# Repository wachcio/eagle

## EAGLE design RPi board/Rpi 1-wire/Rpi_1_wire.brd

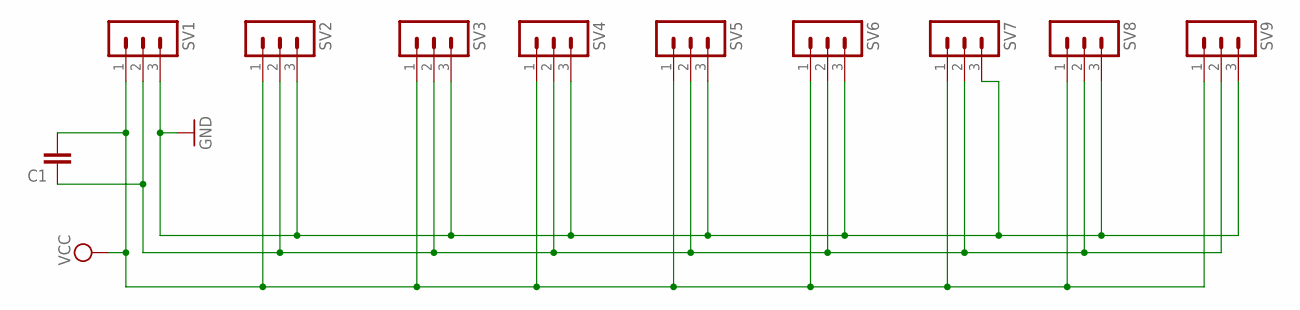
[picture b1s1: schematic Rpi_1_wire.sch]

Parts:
C1: C-EUC0805; C0805
SV1, SV2, SV3, SV4, SV5, SV6, SV7, SV8, SV9: MA03-1

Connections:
GND: SV1.3, SV2.3, SV3.3, SV4.3, SV5.3, SV6.3, SV7.3, SV8.3, SV9.3
unnamed: C1.1, SV1.2, SV2.2, SV3.2, SV4.2, SV5.2, SV6.2, SV7.2, SV8.2, SV9.2
VCC: C1.2, SV1.1, SV2.1, SV3.1, SV4.1, SV5.1, SV6.1, SV7.1, SV8.1, SV9.1

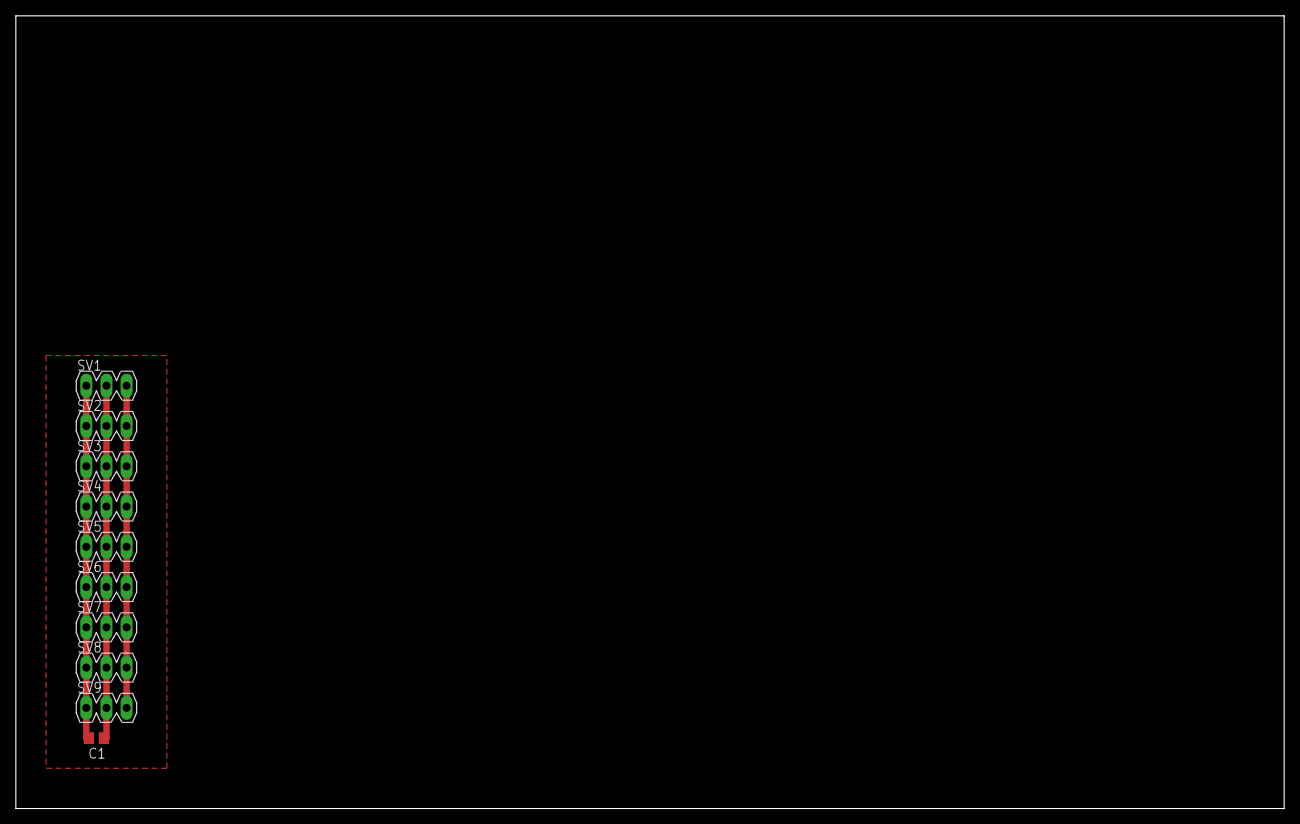
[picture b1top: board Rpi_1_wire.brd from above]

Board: 2 copper layers, 160.0 x 100.0 mm, 10 parts (0 on the bottom side), 3 nets.

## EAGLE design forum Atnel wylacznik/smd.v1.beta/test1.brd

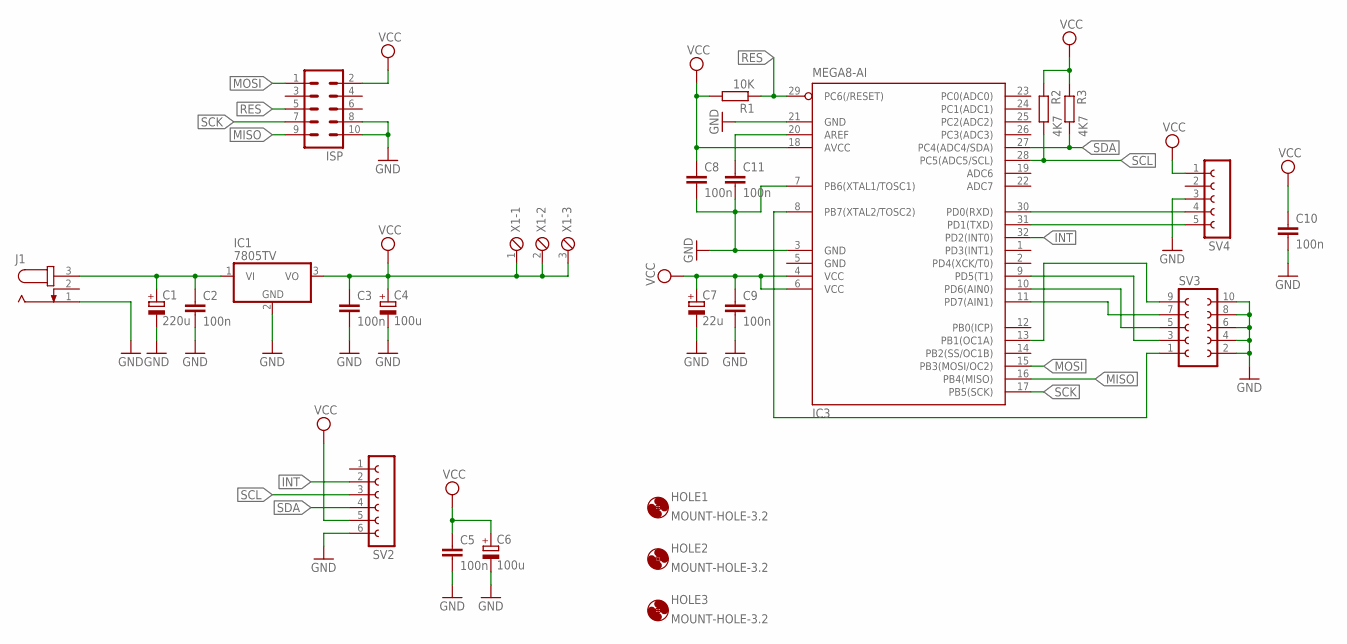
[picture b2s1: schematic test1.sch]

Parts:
C1: 220u; E3,5-8
C2, C3, C5, C8, C9, C10, C11: 100n; C0805
C4, C6: 100u; E2,5-5
C7: 22u; E2,5-5
HOLE1, HOLE2, HOLE3: MOUNT-HOLE-3.2; 3,2
IC1: 7805TV; TO220V
IC3: MEGA8-AI; TQFP32-08
ISP: ML10
J1: JACK-PLUG1; SPC4078
R1: 10K; R0805
R2, R3: 4K7; R0805
SV2: FE06-1; FE06
SV3: FE05-2
SV4: FE05-1
X1: MPT3; 3POL254

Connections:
GND: C1.-, C2.2, C3.2, C4.-, C5.2, C6.-, C7.-, C8.2, C9.2, C10.2, C11.2, IC1.2 (GND), IC3.3 (GND), IC3.5 (GND), IC3.7 (PB6(XTAL1/TOSC1)), IC3.21 (GND), ISP.8, ISP.10, J1.1, SV2.6, SV3.2, SV3.4, SV3.6, SV3.8, SV3.10, SV4.3
INT: IC3.32 (PD2(INT0)), SV2.2
MISO: IC3.16 (PB4(MISO)), ISP.9
MOSI: IC3.15 (PB3(MOSI/OC2)), ISP.1
unnamed: C1.+, C2.1, IC1.1 (VI), J1.3
unnamed: C11.1, IC3.20 (AREF)
unnamed: IC3.30 (PD0(RXD)), SV4.4
unnamed: IC3.31 (PD1(TXD)), SV4.5
unnamed: IC3.8 (PB7(XTAL2/TOSC2)), SV3.1
unnamed: IC3.13 (PB1(OC1A)), SV3.9
unnamed: IC3.11 (PD7(AIN1)), SV3.7
unnamed: IC3.10 (PD6(AIN0)), SV3.5
unnamed: IC3.9 (PD5(T1)), SV3.3
RES: IC3.29 (PC6(/RESET)), ISP.5, R1.1
SCK: IC3.17 (PB5(SCK)), ISP.7
SCL: IC3.28 (PC5(ADC5/SCL)), R2.2, SV2.3
SDA: IC3.27 (PC4(ADC4/SDA)), R3.2, SV2.4
VCC: C3.1, C4.+, C5.1, C6.+, C7.+, C8.1, C9.1, C10.1, IC1.3 (VO), IC3.4 (VCC), IC3.6 (VCC), IC3.18 (AVCC), ISP.2, R1.2, R2.1, R3.1, SV2.5, SV4.1, X1.1, X1.2, X1.3

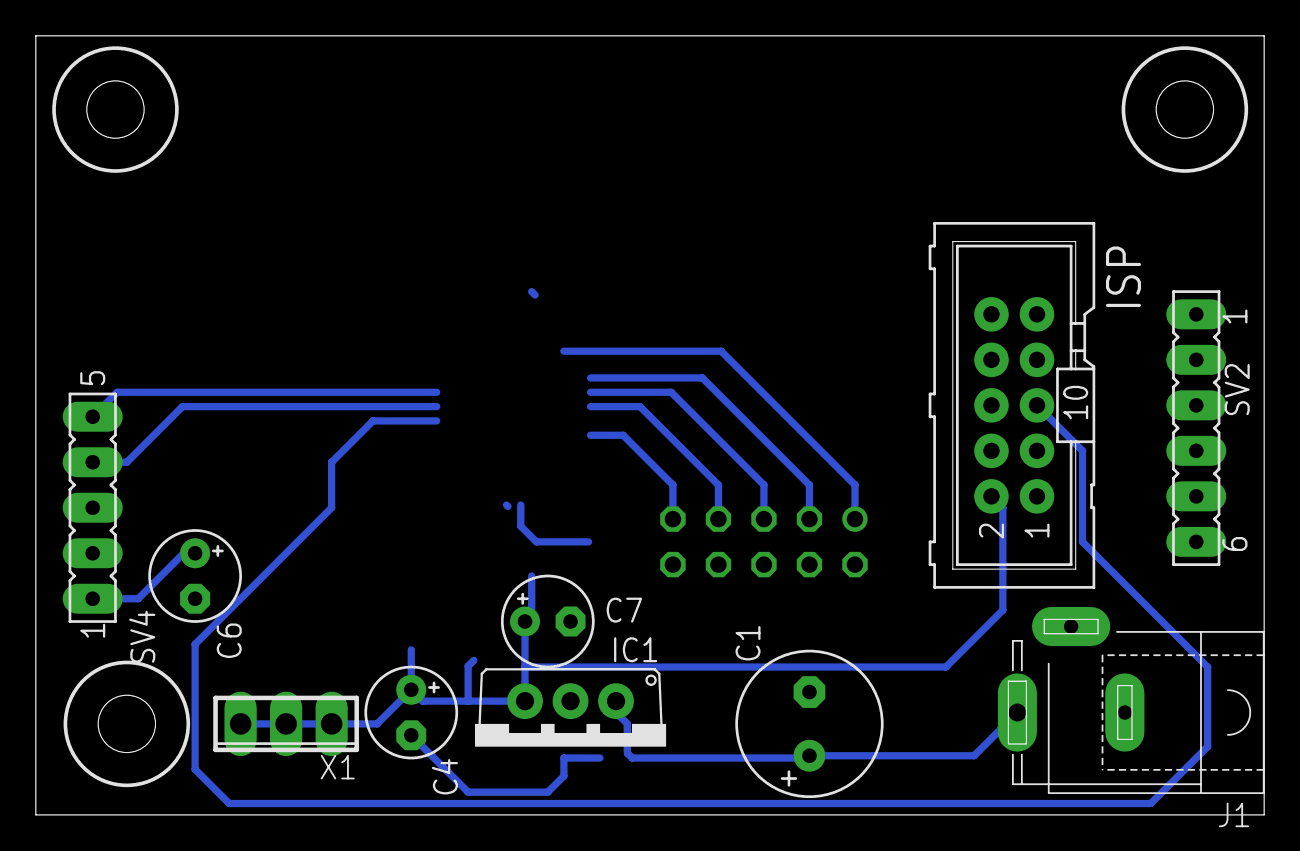
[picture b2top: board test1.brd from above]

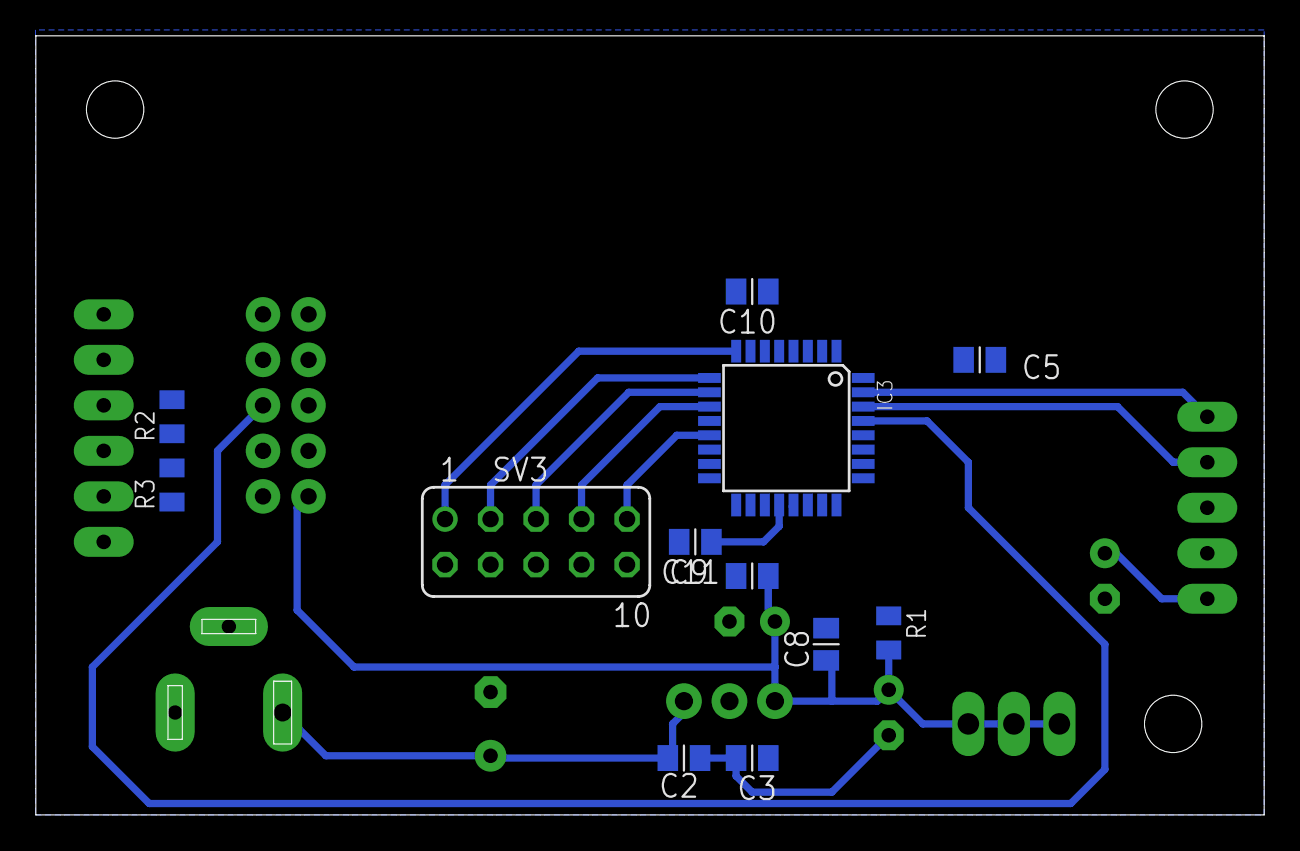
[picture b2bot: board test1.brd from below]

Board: 2 copper layers, 68.6 x 43.5 mm, 25 parts (12 on the bottom side), 18 nets.

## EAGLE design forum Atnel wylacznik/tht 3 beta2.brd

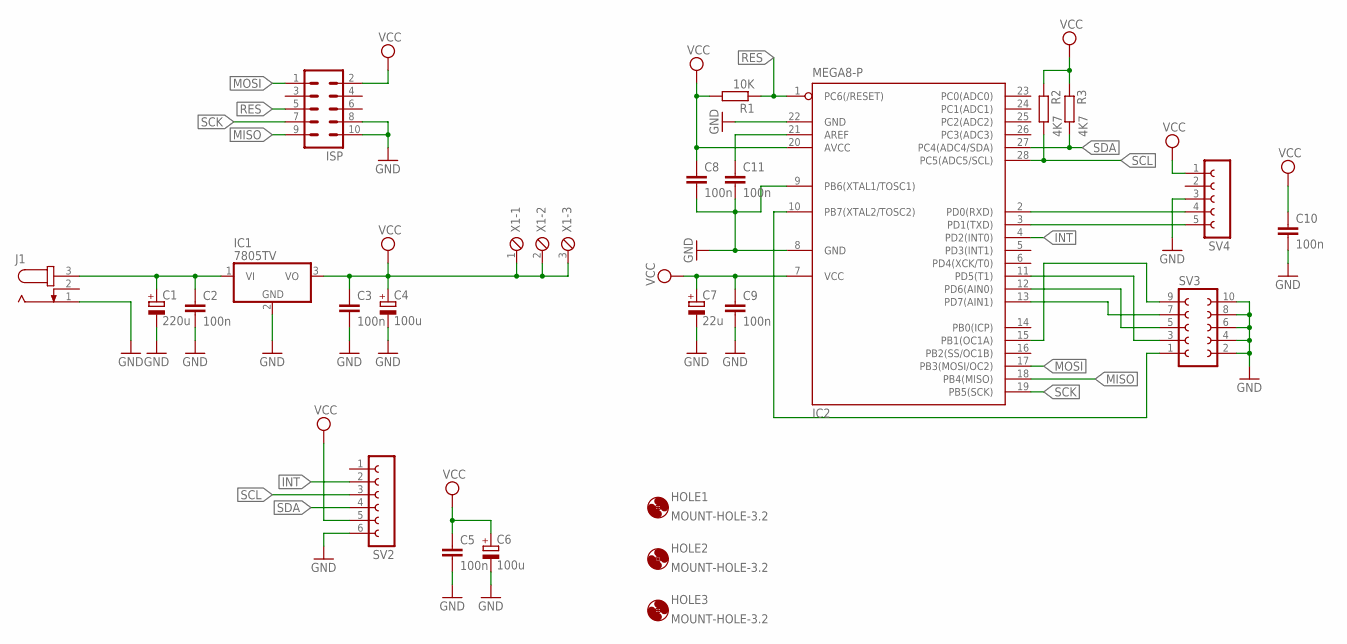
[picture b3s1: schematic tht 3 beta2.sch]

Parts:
C1: 220u; E3,5-8
C2, C3, C5, C8, C10, C11: 100n; C025-025X050
C4, C6: 100u; E2,5-5
C7: 22u; E2,5-5
C9: 100n; C025-030X050
HOLE1, HOLE2, HOLE3: MOUNT-HOLE-3.2; 3,2
IC1: 7805TV; TO220V
IC2: MEGA8-P; DIL28-3
ISP: ML10
J1: JACK-PLUG1; SPC4078
R1: 10K; 0204/7
R2, R3: 4K7; 0204/7
SV2: FE06-1; FE06
SV3: FE05-2
SV4: FE05-1
X1: MPT3; 3POL254

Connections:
GND: C1.-, C2.2, C3.2, C4.-, C5.2, C6.-, C7.-, C8.2, C9.2, C10.2, C11.2, IC1.2 (GND), IC2.8 (GND), IC2.9 (PB6(XTAL1/TOSC1)), IC2.22 (GND), ISP.8, ISP.10, J1.1, SV2.6, SV3.2, SV3.4, SV3.6, SV3.8, SV3.10, SV4.3
INT: IC2.4 (PD2(INT0)), SV2.2
MISO: IC2.18 (PB4(MISO)), ISP.9
MOSI: IC2.17 (PB3(MOSI/OC2)), ISP.1
unnamed: C1.+, C2.1, IC1.1 (VI), J1.3
unnamed: C11.1, IC2.21 (AREF)
unnamed: IC2.2 (PD0(RXD)), SV4.4
unnamed: IC2.3 (PD1(TXD)), SV4.5
unnamed: IC2.10 (PB7(XTAL2/TOSC2)), SV3.1
unnamed: IC2.15 (PB1(OC1A)), SV3.9
unnamed: IC2.13 (PD7(AIN1)), SV3.7
unnamed: IC2.12 (PD6(AIN0)), SV3.5
unnamed: IC2.11 (PD5(T1)), SV3.3
RES: IC2.1 (PC6(/RESET)), ISP.5, R1.1
SCK: IC2.19 (PB5(SCK)), ISP.7
SCL: IC2.28 (PC5(ADC5/SCL)), R2.2, SV2.3
SDA: IC2.27 (PC4(ADC4/SDA)), R3.2, SV2.4
VCC: C3.1, C4.+, C5.1, C6.+, C7.+, C8.1, C9.1, C10.1, IC1.3 (VO), IC2.7 (VCC), IC2.20 (AVCC), ISP.2, R1.2, R2.1, R3.1, SV2.5, SV4.1, X1.1, X1.2, X1.3

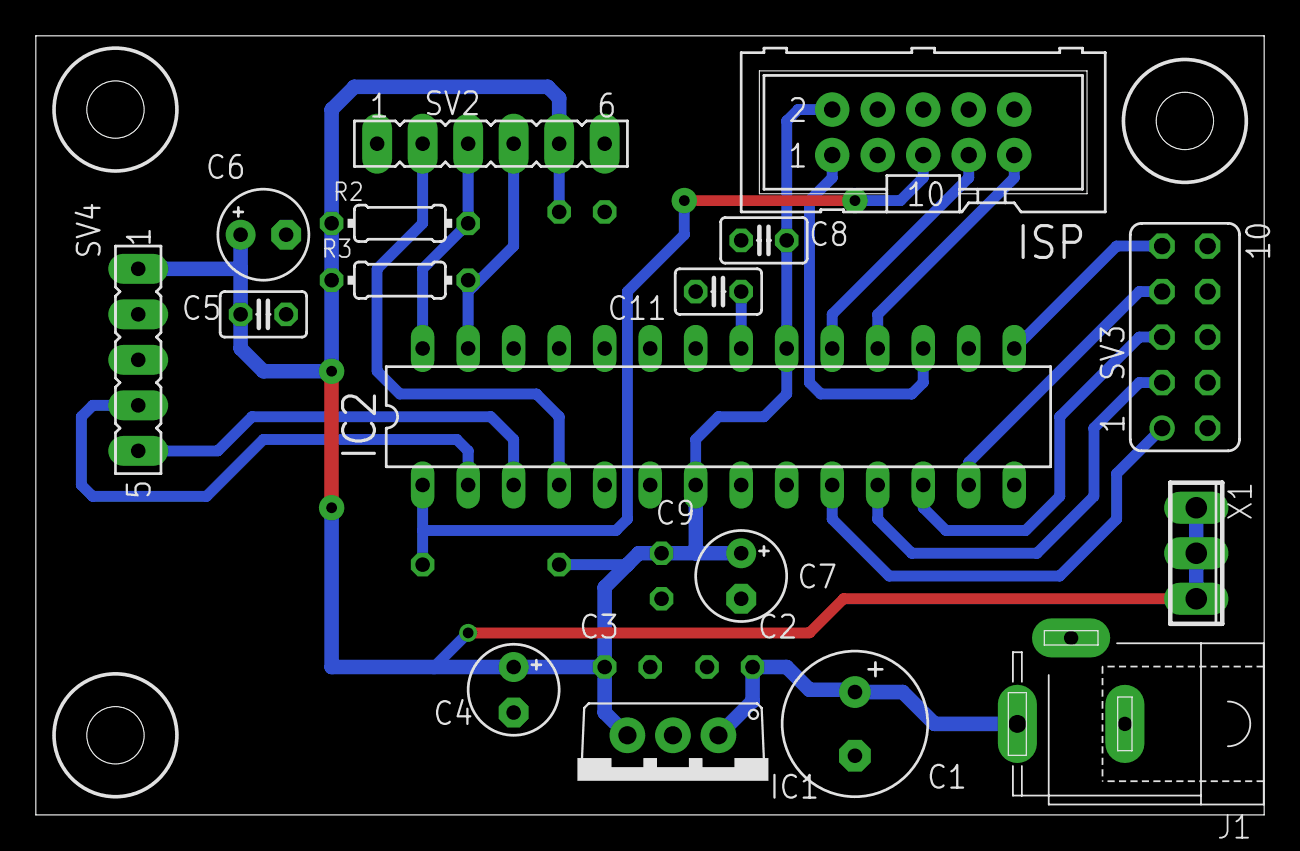
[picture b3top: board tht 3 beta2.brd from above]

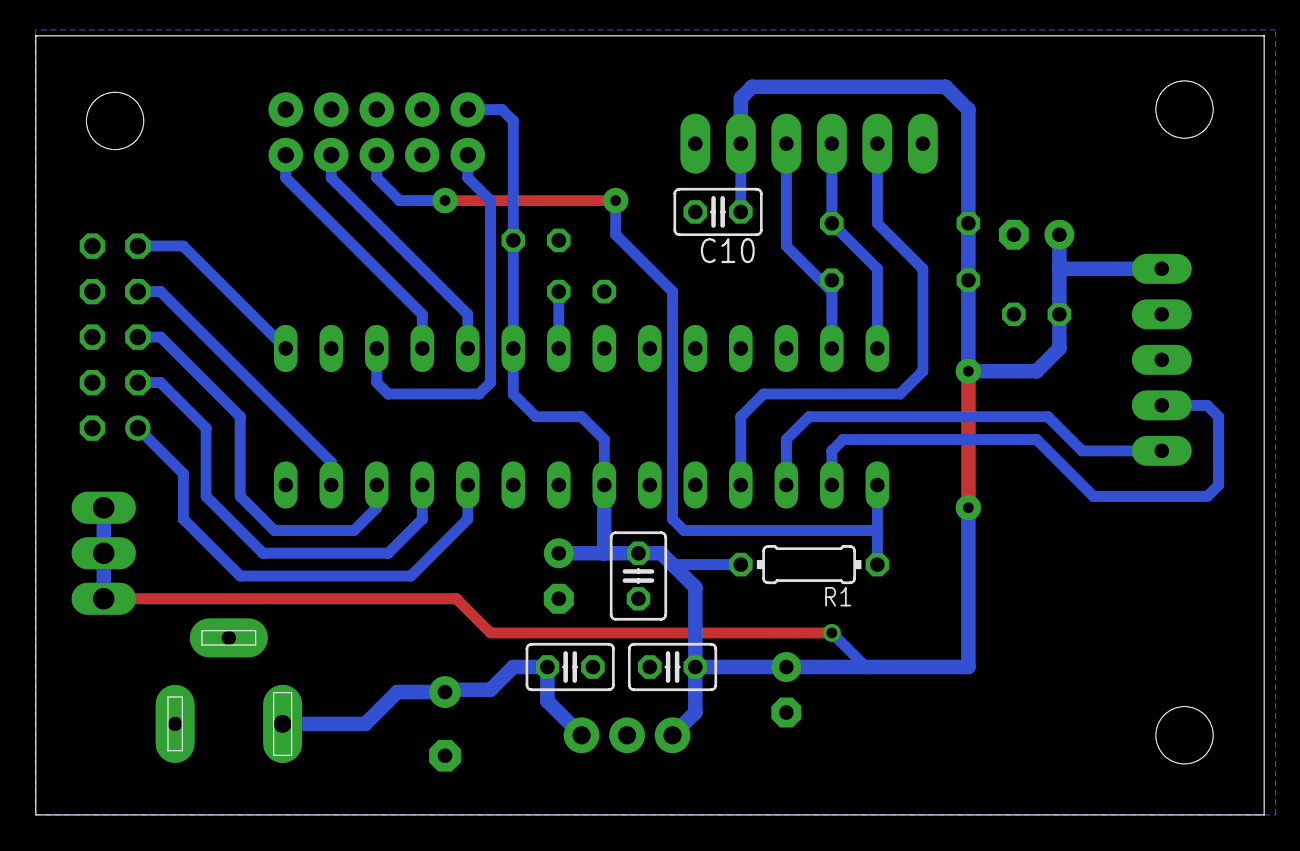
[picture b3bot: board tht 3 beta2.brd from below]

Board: 2 copper layers, 68.6 x 43.5 mm, 25 parts (5 on the bottom side), 18 nets.

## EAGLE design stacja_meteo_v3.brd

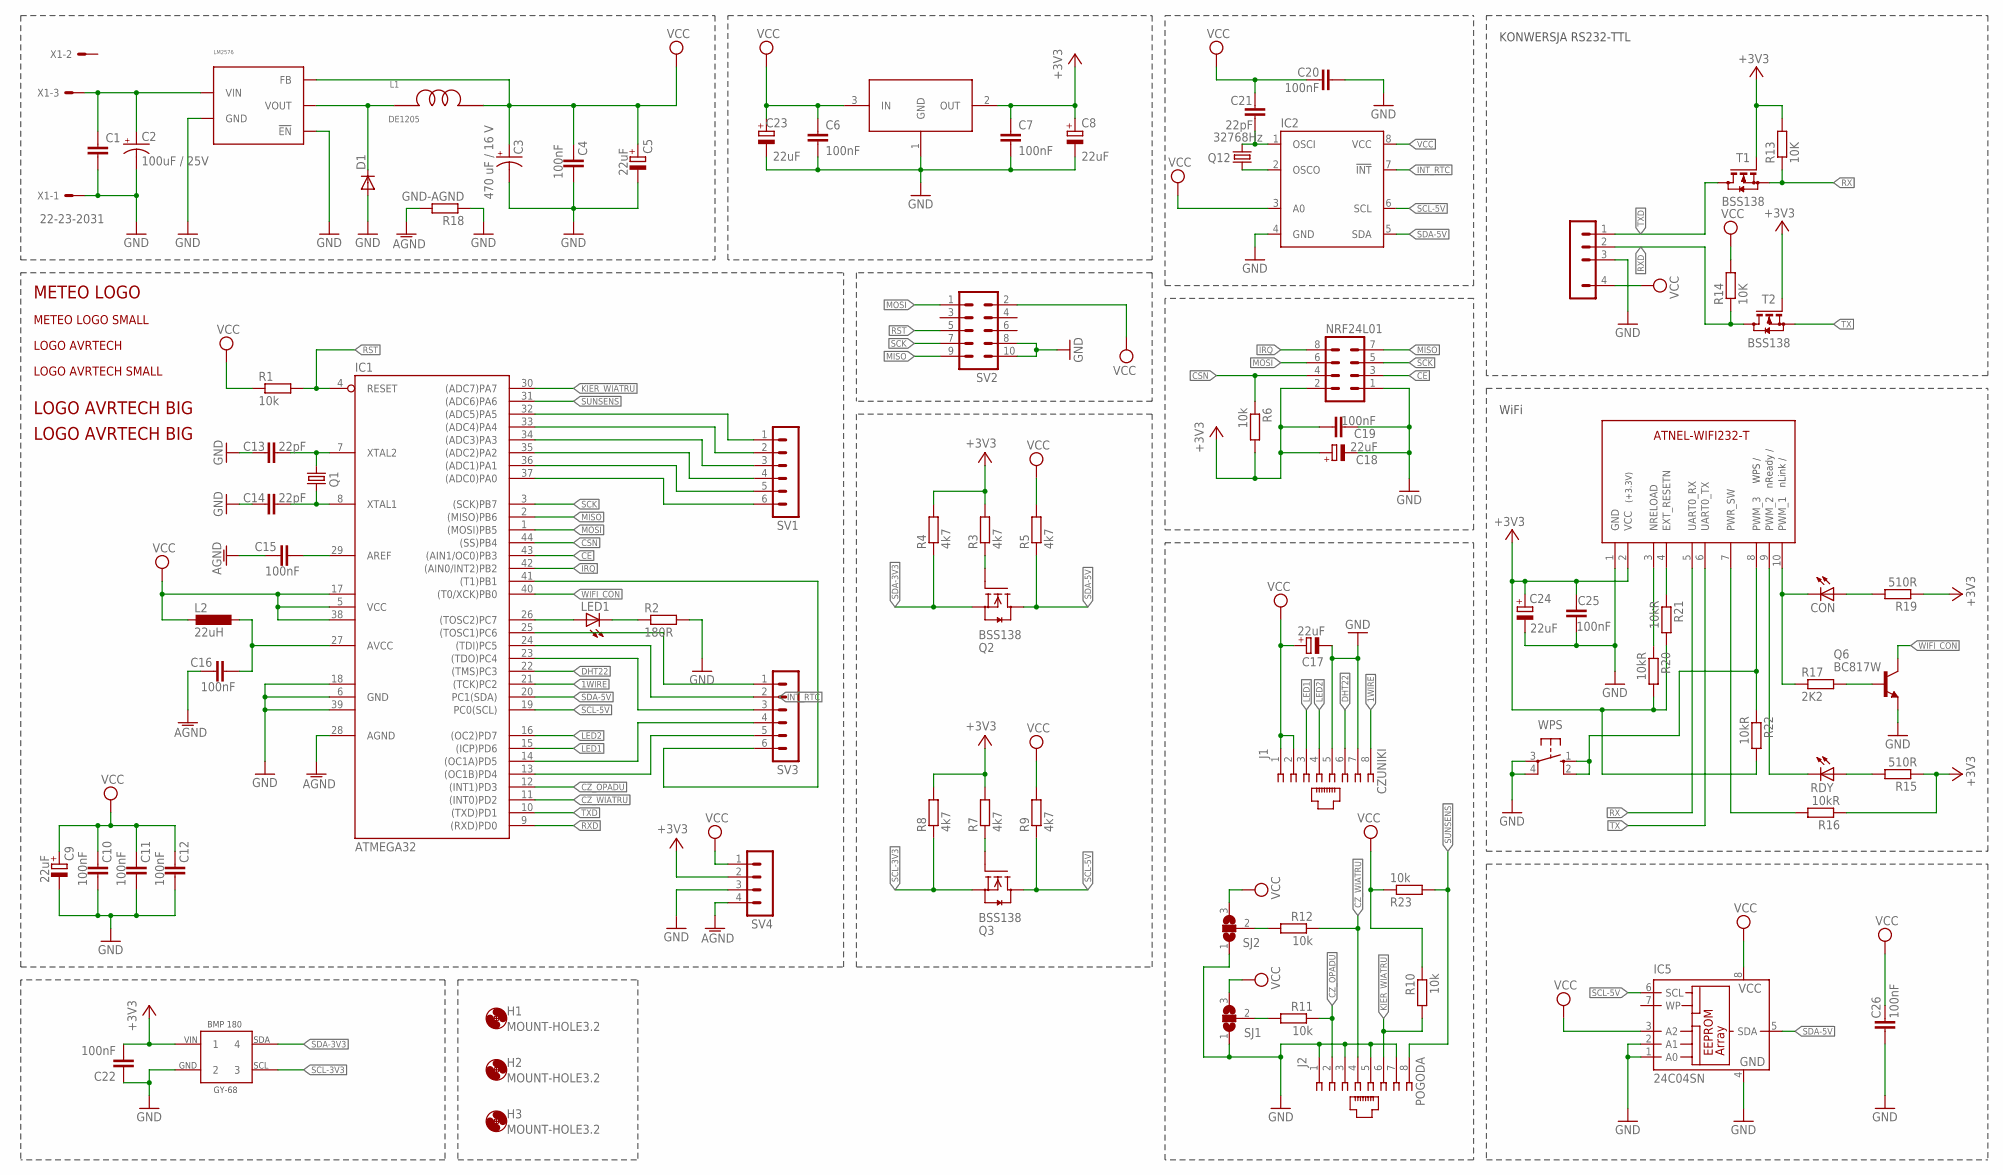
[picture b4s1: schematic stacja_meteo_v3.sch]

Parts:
BMP1: GY-68
C1: C-EUC1206; C1206
C2: 100uF / 25V; PANASONIC_D
C3: 470 uF / 16 V; PANASONIC_E
C4, C10, C11, C12, C15, C16, C22: 100nF; C1206
C5, C8, C9, C17, C18, C23, C24: 22uF; SMC_A
C6, C7, C19, C25: 100nF; C0805
C13, C14: 22pF; C0805K
C20, C26: 100nF; C1206K
C21: 22pF; C1206K
CON: LEDSML0805; SML0805
D1: DIODE-SMC; SMC
H1, H2, H3: MOUNT-HOLE3.2; 3,2
IC1: ATMEGA32; TQFP44
IC2: RTC_PCF8583T; SO08
IC5: 24C04SN; SO-08
J1: CZUNIKI; 556416-1
J2: POGODA; 556416-1
L1: DE1205
L2: 22uH; IR-2
LED1: LED5MM
LM1117/1: LM1117-3.3; SOT223
LM2576: LM2576D2PAK-5; D2PAK-5
NRF24L01: ML10
Q1: 11.059 MHz; CSM-7X-DU
Q2, Q3: BSS138; SOT23
Q6: BC817W; SOT23-BEC
Q12: 32768Hz; MC-406
R1, R10, R11, R12, R23: 10k; R0603
R2: 180R; R0805
R3, R4, R5, R7, R8, R9: 4k7; R0805
R6: 10k; R0805W
R13, R14: 10K; R0805
R15, R19: 510R; R0603
R16, R20, R21, R22: 10kR; R0603
R17: 2K2; R0603
R18: GND-AGND; R0805
RDY: LEDSML0805; SML0805
RS232-TTL: ATB-BTM-222
SJ1, SJ2: SJ2W; SJ_2
SV1, SV3: MA06-1
SV2: ML10
SV4: MA04-1
T1, T2: BSS138; SOT23
U$2: ATNEL-WIFI232-T_2
U$3: METEO_LOGO; LOGO_METEO
U$4: METEO_LOGO_SMALL; LOGO_METEO_SMALL
U$6: LOGO_AVRTECH
U$7: LOGO_AVRTECH_SMALL
U$8, U$9: LOGO_AVRTECH_BIG; LOGOAVRTECHBIG
WPS: 10-XX; B3F-10XX
X1: 22-23-2031

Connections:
1WIRE: IC1.21 ((TCK)PC2), J1.8
+3V3: BMP1.1, C7.1, C8.+, C18.+, C19.1, C22.2, C24.+, C25.1, LM1117/1.2 (OUT), NRF24L01.2, R3.2, R4.2, R6.2, R7.2, R8.2, R13.2, R15.1, R16.1, R19.1, R20.2, R21.2, R22.2, SV4.2, T1.1 (G), T2.1 (G), U$2.2 (VCC)
AGND: C15.1, C16.1, IC1.28 (AGND), R18.2, SV4.4
CE: IC1.43 ((AIN1/OC0)PB3), NRF24L01.3
CSN: IC1.44 ((SS)PB4), NRF24L01.4, R6.1
CZ_OPADU: IC1.12 ((INT1)PD3), J2.2, R11.1
CZ_WIATRU: IC1.11 ((INT0)PD2), J2.4, R12.1
DHT22: IC1.22 ((TMS)PC3), J1.6
GND: BMP1.2, C1.2, C2.-, C3.-, C4.2, C5.-, C6.2, C7.2, C8.-, C9.-, C10.2, C11.2, C12.2, C13.1, C14.1, C17.-, C18.-, C19.2, C20.2, C22.1, C23.-, C24.-, C25.2, C26.2, D1.A, IC1.6 (GND), IC1.18 (GND1), IC1.39 (GND2), IC2.4 (GND), IC5.1 (A0), IC5.2 (A1), IC5.4 (GND), J1.5, J1.7, J2.1, J2.3, J2.5, J2.7, LM1117/1.1 (GND), LM2576.P$3 (GND), LM2576.P$5 (!EN), LM2576.P$6 (GND), NRF24L01.1, Q6.E, R2.2, R18.1, RS232-TTL.3 (GND), SJ1.1, SJ2.1, SV2.8, SV2.10, SV4.3, U$2.1 (GND), WPS.3, WPS.4 (P1), X1.1
INT_RTC: IC1.24 ((TDI)PC5), IC2.7 (!INT), SV3.2
IRQ: IC1.42 ((AIN0/INT2)PB2), NRF24L01.8
KIER_WIATRU: IC1.30 ((ADC7)PA7), J2.6, R10.2
LED1: IC1.15 ((ICP)PD6), J1.3
LED2: IC1.16 ((OC2)PD7), J1.4
MISO: IC1.2 ((MISO)PB6), NRF24L01.7, SV2.9
MOSI: IC1.1 ((MOSI)PB5), NRF24L01.6, SV2.1
unnamed: C15.2, IC1.29 (AREF)
unnamed: IC1.26 ((TOSC2)PC7), LED1.A
unnamed: C16.2, IC1.27 (AVCC), L2.1
unnamed: LED1.K (C), R2.1
unnamed: Q2.1 (G), R3.1
unnamed: C13.2, IC1.7 (XTAL2), Q1.2
unnamed: C14.2, IC1.8 (XTAL1), Q1.1
unnamed: R15.2, RDY.A
unnamed: R12.2, SJ2.2
unnamed: R11.2, SJ1.2
unnamed: RDY.C, U$2.9 (PWM_2)
unnamed: Q3.1 (G), R7.1
unnamed: R16.2, U$2.7 (PWR_SW)
unnamed: R20.1, U$2.3 (NRELOAD)
unnamed: R21.1, U$2.4 (EXT_RESETN)
unnamed: IC1.32 ((ADC5)PA5), SV1.1
unnamed: Q6.B, R17.2
unnamed: IC1.33 ((ADC4)PA4), SV1.2
unnamed: R22.1, U$2.8 (PWM_3), WPS.1 (S), WPS.2 (S1)
unnamed: IC1.34 ((ADC3)PA3), SV1.3
unnamed: IC1.35 ((ADC2)PA2), SV1.4
unnamed: IC1.36 ((ADC1)PA1), SV1.5
unnamed: CON.A, R19.2
unnamed: IC1.37 ((ADC0)PA0), SV1.6
unnamed: IC1.41 ((T1)PB1), SV3.6
unnamed: IC1.25 ((TOSC1)PC6), SV3.1
unnamed: IC1.23 ((TDO)PC4), SV3.3
unnamed: IC1.14 ((OC1A)PD5), SV3.4
unnamed: IC1.13 ((OC1B)PD4), SV3.5
unnamed: D1.C, L1.P$1, LM2576.P$2 (VOUT)
unnamed: C1.1, C2.+, LM2576.P$1 (VIN), X1.3
unnamed: IC2.2 (OSCO), Q12.2
OSCI1: C21.2, IC2.1 (OSCI), Q12.1
PWM_1: CON.C, R17.1, U$2.10 (PWM_1)
RST: IC1.4 (RESET), R1.2, SV2.5
RX: R13.1, T1.2 (S), U$2.5 (UART0_RX)
RXD: IC1.9 ((RXD)PD0), R14.1, RS232-TTL.2 (TX), T2.3 (D)
SCK: IC1.3 ((SCK)PB7), NRF24L01.5, SV2.7
SCL-3V3: BMP1.3, Q3.2 (S), R8.1
SCL-5V: IC1.19 (PC0(SCL)), IC2.6 (SCL), IC5.6 (SCL), Q3.3 (D), R9.1
SDA-3V3: BMP1.4, Q2.2 (S), R4.1
SDA-5V: IC1.20 (PC1(SDA)), IC2.5 (SDA), IC5.5 (SDA), Q2.3 (D), R5.1
SUNSENS: IC1.31 ((ADC6)PA6), J2.8, R23.2
TX: T2.2 (S), U$2.6 (UART0_TX)
TXD: IC1.10 ((TXD)PD1), RS232-TTL.1 (RX), T1.3 (D)
VCC: C3.+, C4.1, C5.+, C6.1, C9.+, C10.1, C11.1, C12.1, C17.+, C20.1, C21.1, C23.+, C26.1, IC1.5 (VCC), IC1.17 (VCC1), IC1.38 (VCC2), IC2.3 (A0), IC2.8 (VCC), IC5.3 (A2), IC5.8 (VCC), J1.1, J1.2, L1.P$3, L2.2, LM1117/1.3 (IN), LM2576.P$4 (FB), R1.1, R5.2, R9.2, R10.1, R14.2, R23.1, RS232-TTL.4 (VCC), SJ1.3, SJ2.3, SV2.2, SV4.1
WIFI_CON: IC1.40 ((T0/XCK)PB0), Q6.C

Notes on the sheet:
KONWERSJA RS232-TTL
WiFi

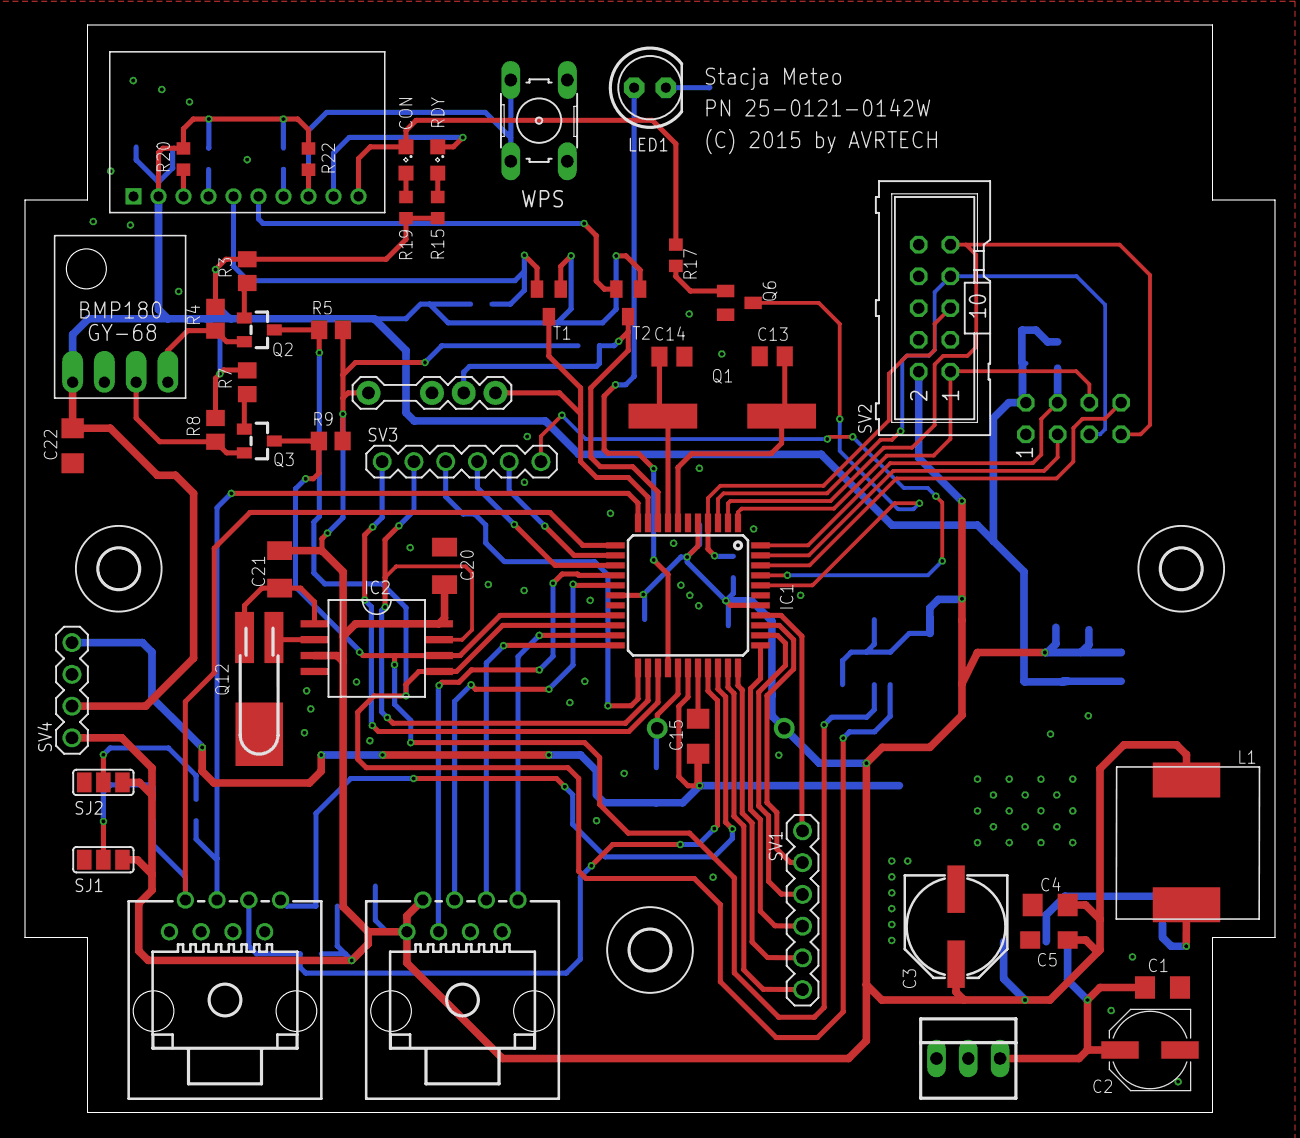
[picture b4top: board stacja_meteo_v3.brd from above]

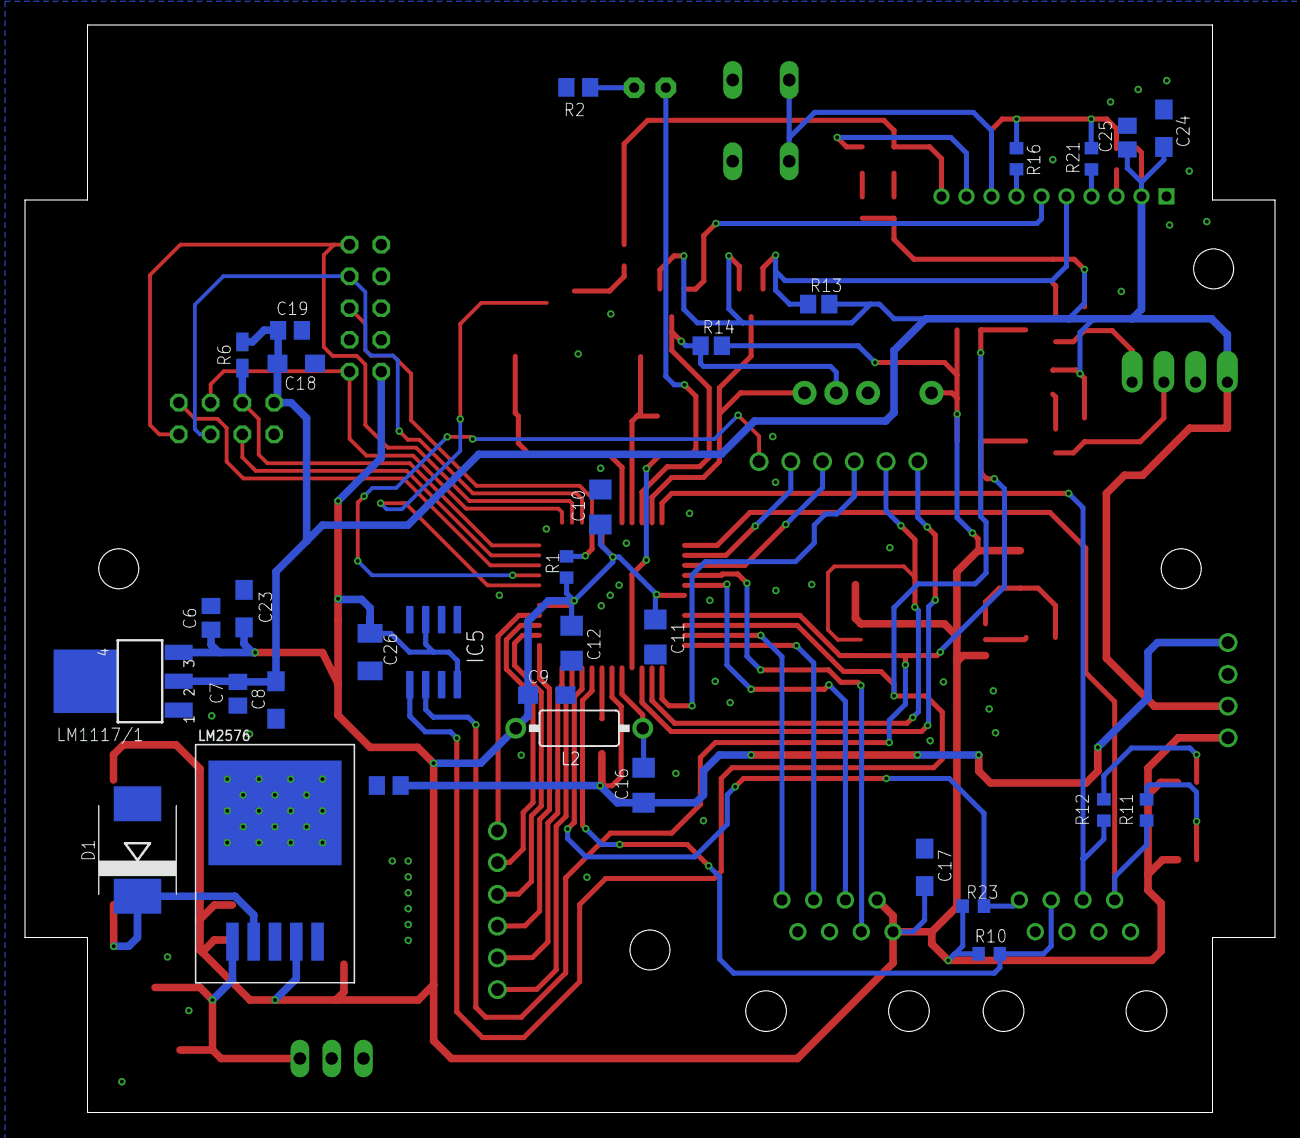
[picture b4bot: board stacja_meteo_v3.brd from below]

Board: 2 copper layers, 100.0 x 87.0 mm, 90 parts (34 on the bottom side), 63 nets.

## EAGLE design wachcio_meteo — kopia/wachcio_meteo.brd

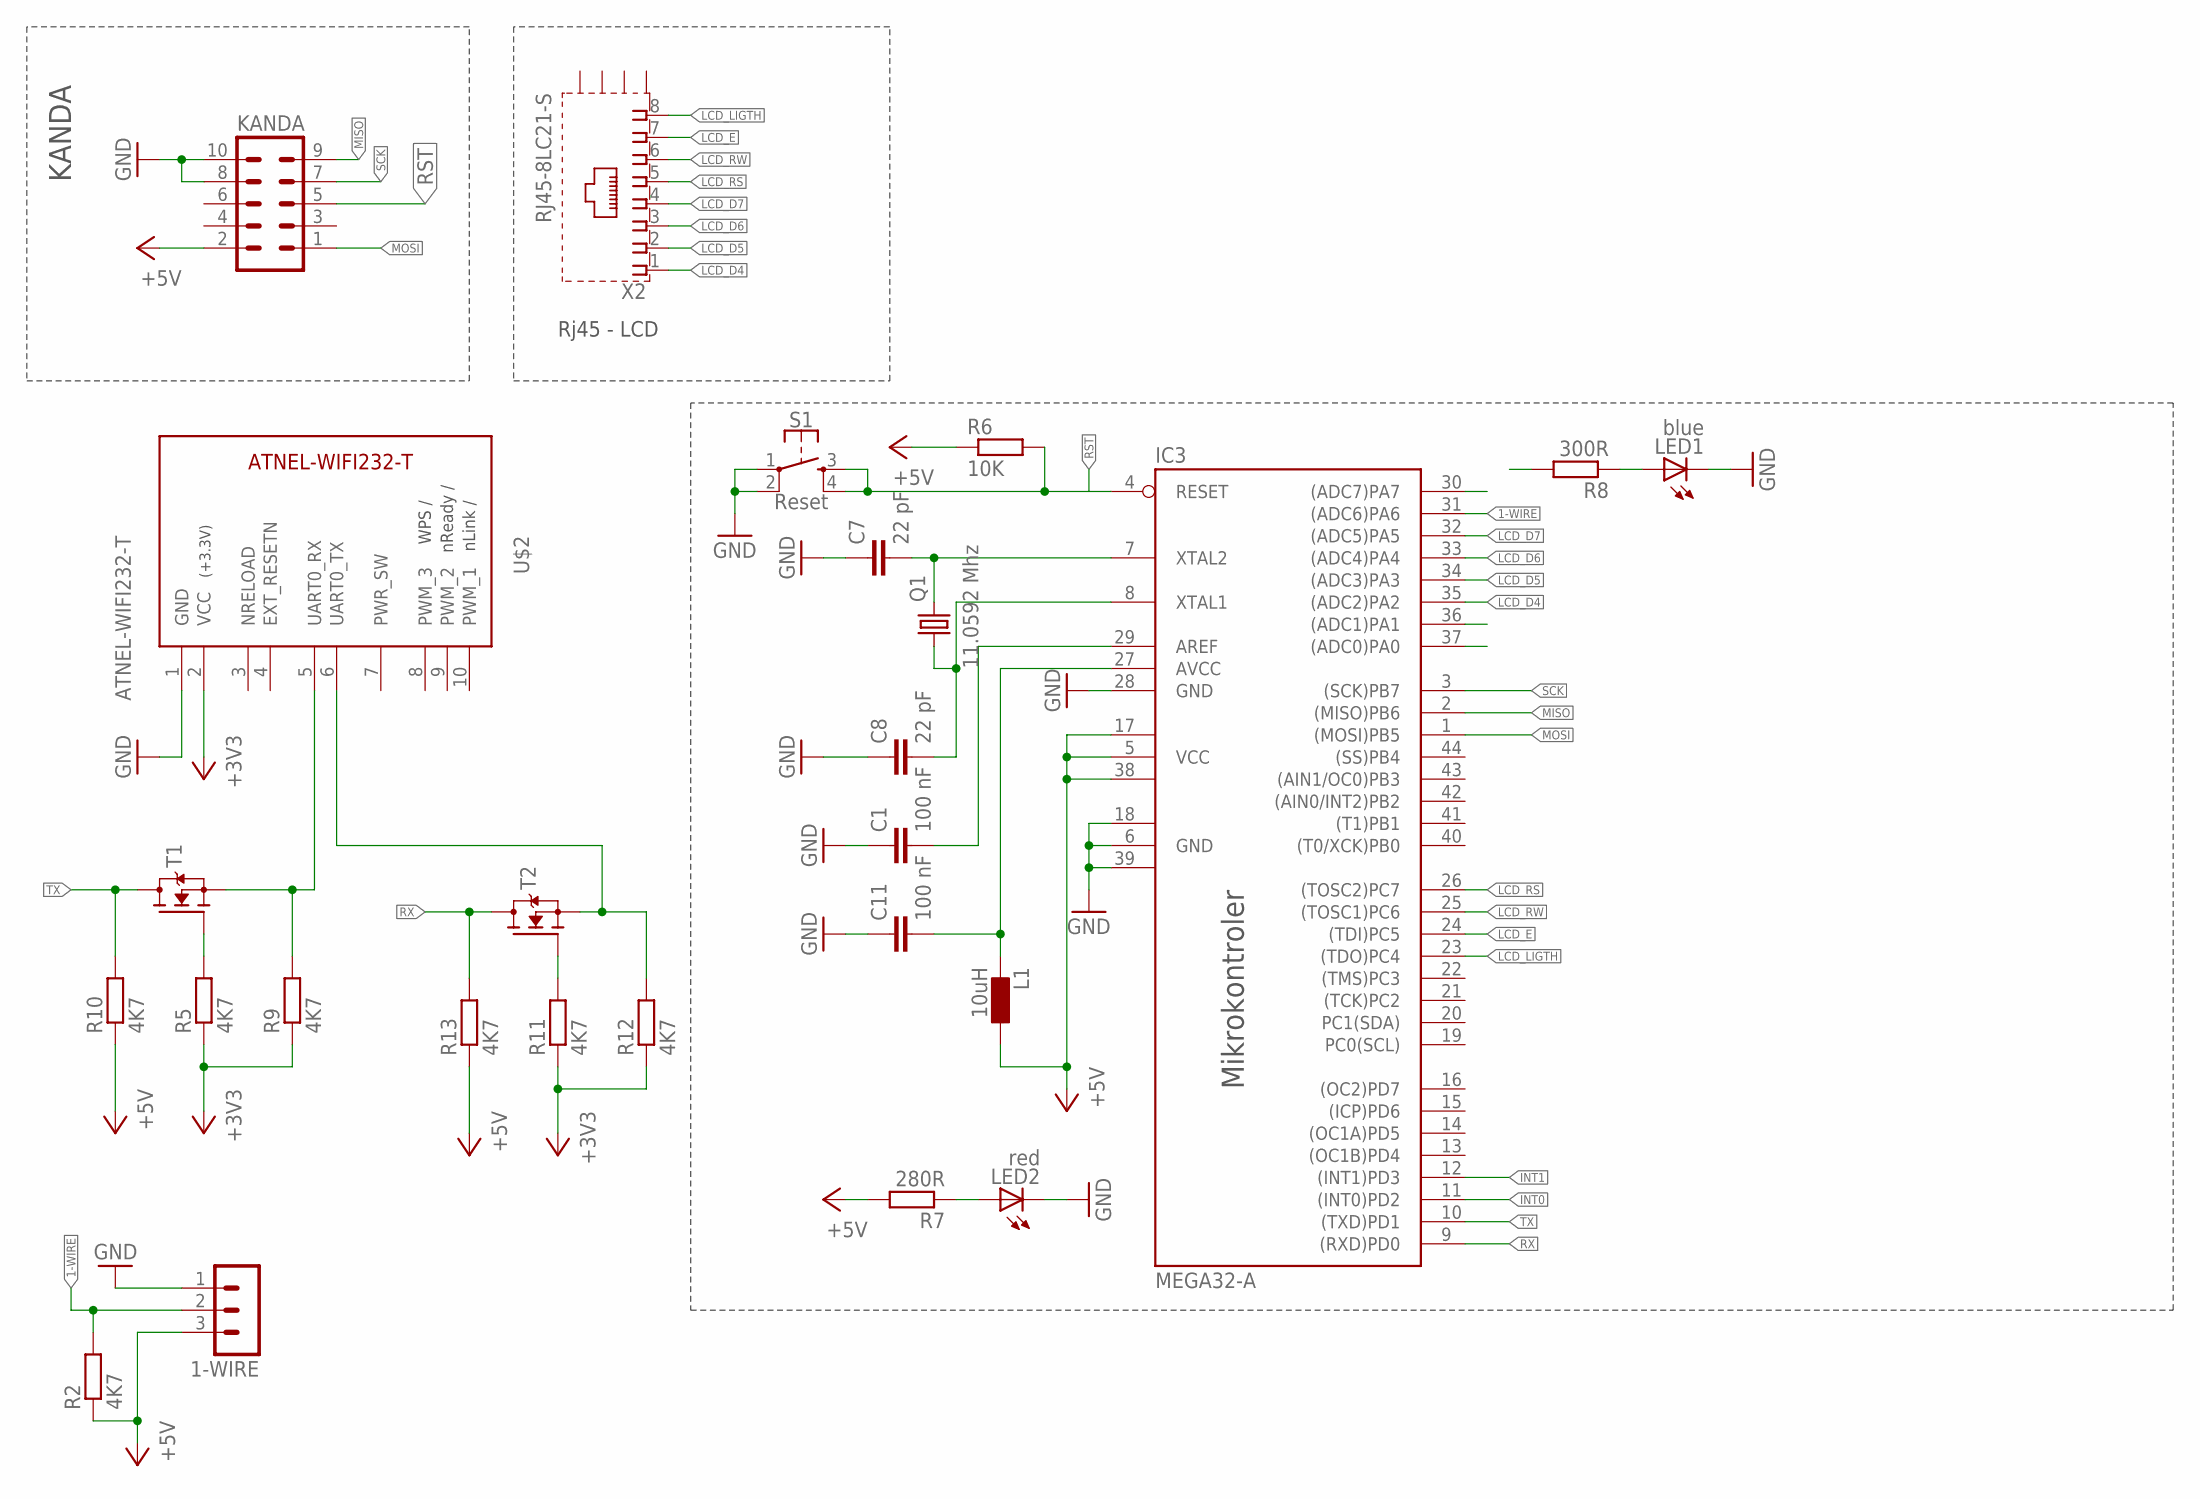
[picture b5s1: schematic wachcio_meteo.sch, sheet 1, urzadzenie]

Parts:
1-WIRE: MA03-1
C1, C11: 100 nF; C0805
C7, C8: 22 pF; C0805
IC3: MEGA32-A; TQFP44
KANDA: ML10
L1: 10uH; L3230M
LED1: blue; CHIPLED_1206
LED2: red; CHIPLED_1206
Q1: 11.0592 Mhz; SM49
R2, R5, R9, R10, R11, R12, R13: 4K7; R1206W
R6: 10K; R1206W
R7: 280R; R1206W
R8: 300R; R1206W
S1: Reset; TACTILE_SWITCH_SMD_4.6X2.8MM
T1, T2: MOSFET-N-SOT23; SOT23
U$2: ATNEL-WIFI232-T
X2: RJ45-8LC21-S; RJ45-SHIELD1

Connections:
1-WIRE: 1-WIRE.2, IC3.31 ((ADC6)PA6), R2.2
+3V3: R5.1, R9.1, R11.1, R12.1, U$2.2 (VCC); also elsewhere on the board
+5V: 1-WIRE.3, IC3.5 (VCC), IC3.17 (VCC1), IC3.38 (VCC2), KANDA.2, L1.1, R2.1, R6.1, R7.2, R10.1, R13.1; also elsewhere on the board
GND: 1-WIRE.1, C1.1, C7.1, C8.1, C11.1, IC3.6 (GND), IC3.18 (GND1), IC3.28 (GND), IC3.39 (GND2), KANDA.8, KANDA.10, LED1.C, LED2.C, S1.1, S1.2, U$2.1 (GND); also elsewhere on the board
INT0: IC3.11 ((INT0)PD2)
INT1: IC3.12 ((INT1)PD3)
LCD_D4: IC3.35 ((ADC2)PA2), X2.1
LCD_D5: IC3.34 ((ADC3)PA3), X2.2
LCD_D6: IC3.33 ((ADC4)PA4), X2.3
LCD_D7: IC3.32 ((ADC5)PA5), X2.4
LCD_E: IC3.24 ((TDI)PC5), X2.7
LCD_LIGTH: IC3.23 ((TDO)PC4), X2.8
LCD_RS: IC3.26 ((TOSC2)PC7), X2.5
LCD_RW: IC3.25 ((TOSC1)PC6), X2.6
MISO: IC3.2 ((MISO)PB6), KANDA.9
MOSI: IC3.1 ((MOSI)PB5), KANDA.1
unnamed: R9.2, T1.2 (S), U$2.5 (UART0_RX)
unnamed: C11.2, IC3.27 (AVCC), L1.2
unnamed: C1.2, IC3.29 (AREF)
unnamed: R5.2, T1.1 (G)
unnamed: R12.2, T2.2 (S), U$2.6 (UART0_TX)
unnamed: C7.2, IC3.7 (XTAL2), Q1.2
unnamed: C8.2, IC3.8 (XTAL1), Q1.1
unnamed: LED2.A, R7.1
unnamed: LED1.A, R8.1
unnamed: R11.2, T2.1 (G)
RST: IC3.4 (RESET), KANDA.5, R6.2, S1.3, S1.4
RX: IC3.9 ((RXD)PD0), R13.2, T2.3 (D)
SCK: IC3.3 ((SCK)PB7), KANDA.7
TX: IC3.10 ((TXD)PD1), R10.2, T1.3 (D)

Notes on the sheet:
KANDA
Mikrokontroler
Rj45 - LCD

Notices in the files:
stacja_meteo_v3.brd:
(C) 2015 by AVRTECH
parts and their libraries:
SparkFun-Capacitors: Licensing: Creative Commons ShareAlike 4.0 International - https://creativecommons.org/licenses/by-sa/4.0
m-pad-2.1: License : GNU General Public License version 2 (see bottom)
FaBo-Sensor: Released under the Creative Commons Attribution-ShareAlike 4.0 License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
